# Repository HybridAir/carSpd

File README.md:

# carSpd

The carSpd (name in progress) is a work in progress device used to display your car's speed and other data in an easy to read, digital format. To do this, the device takes advantage of your car's speed and injector signals, much like the [MPGuino](http://ecomodder.com/wiki/index.php/MPGuino) project. Planned features include imperial/metric support, gas mileage and time display, and probably more depending on feature creep.

My main motivation for starting this project is so that I wont have to read the tiny kph numbers on my car's speedometer, since I just moved to Canada from the US with my car.

*This project is meant to be some kind of successor to the canceled carbt_v1 project. While their main functions are very different, they both serve the purpose of improving or adding new functions to my car.*

## Todo
- Finish programming
- Documentation
- Assemble

## Used Libraries
[Button](https://github.com/JChristensen/Button)

[EEPROMEx](https://github.com/thijse/Arduino-EEPROMEx)

[ST7032](https://github.com/tomozh/arduino_ST7032)

[RTC](https://github.com/Makuna/Rtc)

[RunningAverage](https://github.com/RobTillaart/Arduino/tree/master/libraries/RunningAverage)

[OneWire](https://github.com/PaulStoffregen/OneWire)

[DallasTemperature](https://github.com/milesburton/Arduino-Temperature-Control-Library)

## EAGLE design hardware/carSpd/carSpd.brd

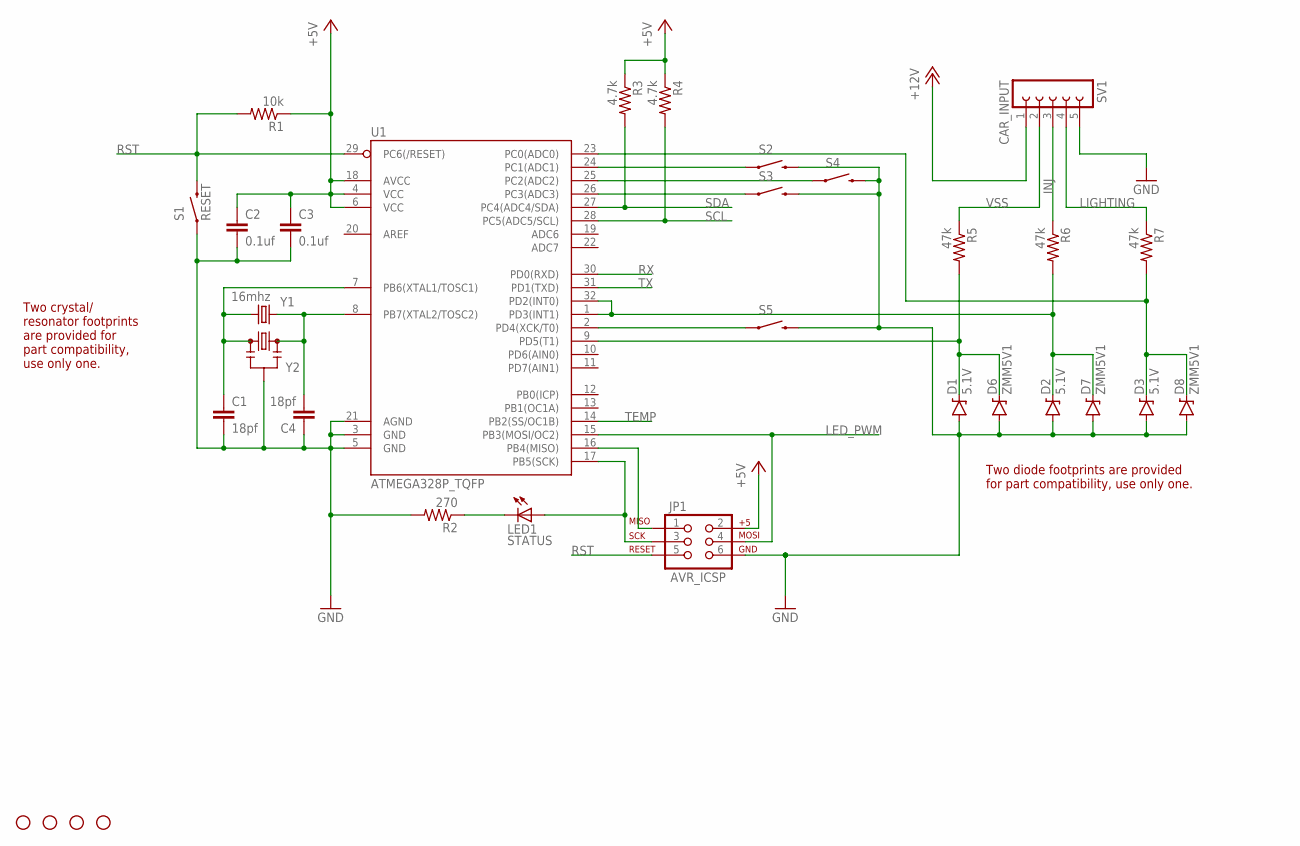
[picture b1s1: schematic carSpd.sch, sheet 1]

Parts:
C1, C4: 18pf; C0603K
C2, C3: 0.1uf; C0603K
D1, D2, D3: 5.1V; SOD-323
D6, D7, D8: ZMM5V1; SOD-80
H1, H2, H3, H4: STAND-OFF
JP1: AVR_ICSP; 2X3_TEST_POINTS
LED1: STATUS; CHIPLED_0805
R1: 10k; R0603
R2: 270; R0603
R3, R4: 4.7k; R0805
R5, R6, R7: 47k; R0805
S1: RESET; TACTILE-SWITCH-1101NE
S2, S3, S4, S5: SWITCH-MOMENTARY-2SMD-1101NE; TACTILE-SWITCH-1101NE
SV1: CAR_INPUT; FE05W
U1: ATMEGA328P_TQFP; TQFP32-08
Y1: 16mhz; CRYSTAL-SMD-5X3
Y2: 16MHZ; RESONATOR-SMD

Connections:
+5V: C2.1, C3.1, JP1.2, R1.1, R3.1, R4.1, U1.4 (VCC), U1.6 (VCC), U1.18 (AVCC); also elsewhere on the board
+12V: SV1.1; also elsewhere on the board
GND: C1.2, C2.2, C3.2, C4.1, D1.A, D2.A, D3.A, D6.A, D7.A, D8.A, JP1.6, R2.2, S1.1, S2.2, S3.2, S4.2, S5.2, SV1.5, U1.3 (GND), U1.5 (GND), U1.21 (AGND), Y2.2; also elsewhere on the board
INJ: R6.1, SV1.3
LED_PWM: JP1.4, U1.15 (PB3(MOSI/OC2)); also elsewhere on the board
LIGHTING: R7.1, SV1.4
unnamed: S2.1, U1.24 (PC1(ADC1))
unnamed: S4.1, U1.25 (PC2(ADC2))
unnamed: S3.1, U1.26 (PC3(ADC3))
unnamed: S5.1, U1.2 (PD4(XCK/T0))
unnamed: JP1.1, U1.16 (PB4(MISO))
unnamed: C1.1, U1.7 (PB6(XTAL1/TOSC1)), Y1.3 (2), Y2.1
unnamed: JP1.3, LED1.A, U1.17 (PB5(SCK))
unnamed: D2.C, D7.C, R6.2, U1.1 (PD3(INT1)), U1.32 (PD2(INT0))
unnamed: D3.C, D8.C, R7.2, U1.23 (PC0(ADC0))
unnamed: LED1.C, R2.1
unnamed: D1.C, D6.C, R5.2, U1.9 (PD5(T1))
unnamed: C4.2, U1.8 (PB7(XTAL2/TOSC2)), Y1.1, Y2.3
RST: JP1.5, R1.2, S1.2, U1.29 (PC6(/RESET)); also elsewhere on the board
RX: U1.30 (PD0(RXD)); also elsewhere on the board
SCL: R4.2, U1.28 (PC5(ADC5/SCL)); also elsewhere on the board
SDA: R3.2, U1.27 (PC4(ADC4/SDA)); also elsewhere on the board
TEMP: U1.14 (PB2(SS/OC1B)); also elsewhere on the board
TX: U1.31 (PD1(TXD)); also elsewhere on the board
VSS: R5.1, SV1.2

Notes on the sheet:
Two diode footprints are provided for part compatibility, use only one.
Two crystal/ resonator footprints are provided for part compatibility, use only one.

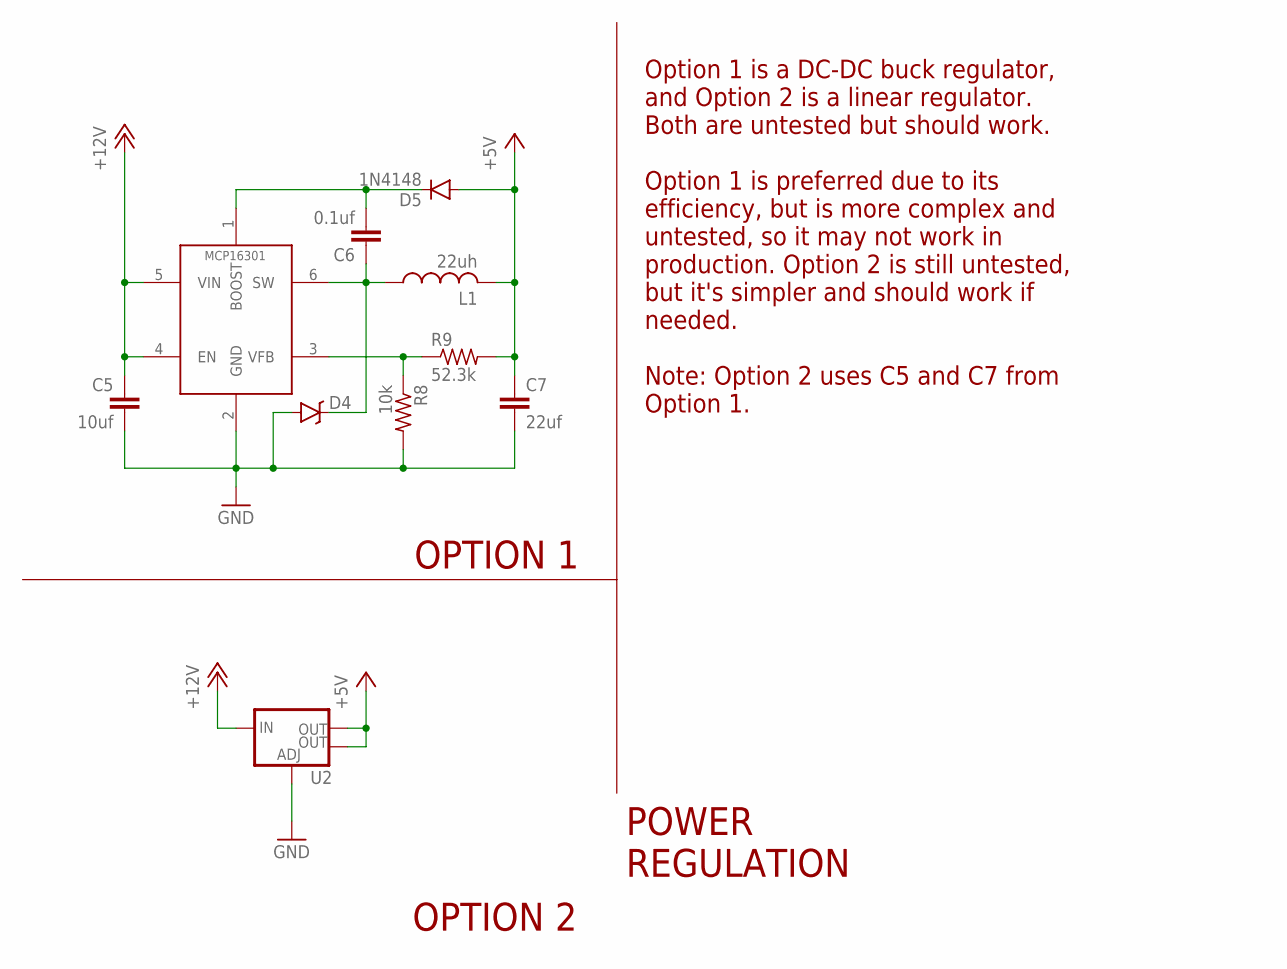
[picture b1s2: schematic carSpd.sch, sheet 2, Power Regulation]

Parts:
C5: 10uf; C0603K
C6: 0.1uf; C0603K
C7: 22uf; C0603K
D4: DIODE-SCHOTTKY-BAT20J; SOD-323
D5: 1N4148; SOD-323
IC1: MCP16301/H; SOT23-6
L1: 22uh; IND-1007/2518
R8: 10k; R0603
R9: 52.3k; R0603
U2: V_REG_LM1117SOT223; SOT223

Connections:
+5V: C7.1, D5.A, L1.P$2 (2), R9.2, U2.2 (OUT), U2.4 (OUT); also elsewhere on the board
+12V: C5.1, IC1.4 (EN), IC1.5 (VIN), U2.3 (IN); also elsewhere on the board
GND: C5.2, C7.2, D4.A, IC1.2 (GND), R8.2, U2.1 (ADJ); also elsewhere on the board
unnamed: IC1.3 (VFB), R8.1, R9.1
unnamed: C6.1, D4.C, IC1.6 (SW), L1.P$1 (1)
unnamed: C6.2, D5.C, IC1.1 (BOOST)

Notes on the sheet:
POWER REGULATION
Option 1 is a DC-DC buck regulator, and Option 2 is a linear regulator. Both are untested but should work. Option 1 is preferred due to its efficiency, but is more complex and untested, so it may not work in production. Option 2 is still untested, but it's simpler and should work if needed. Note: O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
OPTION 1
OPTION 2
MCP16301

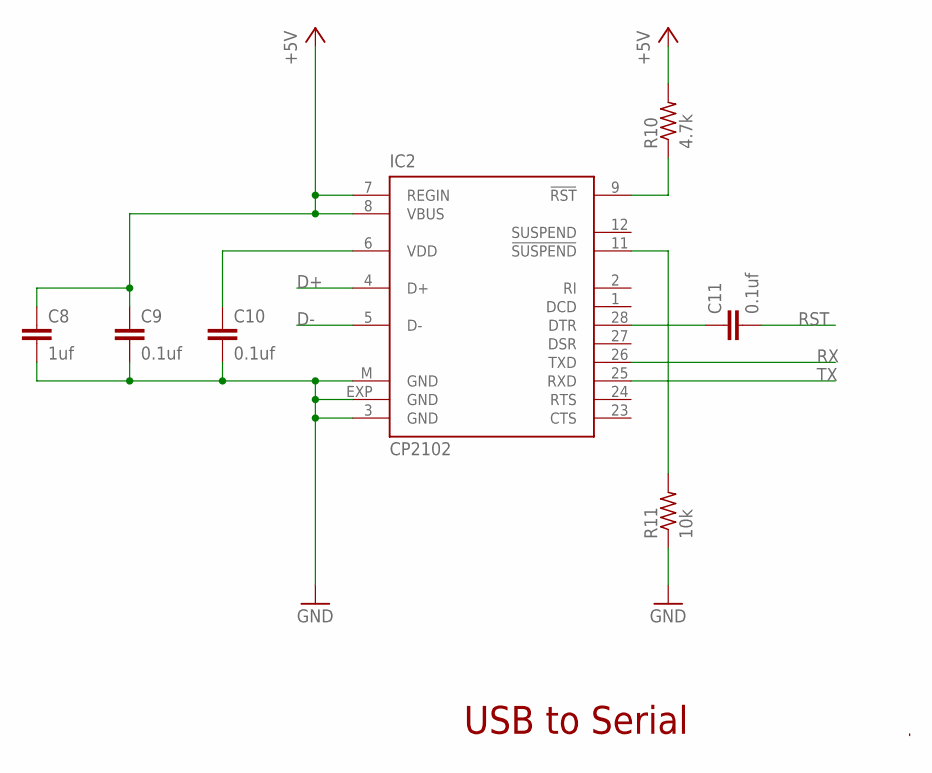
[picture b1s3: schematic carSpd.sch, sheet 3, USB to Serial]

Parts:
C8: 1uf; C0805K
C9, C10, C11: 0.1uf; C0603K
IC2: CP2102; MLP28
R10: 4.7k; R0805
R11: 10k; R0603

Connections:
+5V: C8.1, C9.1, IC2.7 (REGIN), IC2.8 (VBUS), R10.2; also elsewhere on the board
D+: IC2.4 (D+); also elsewhere on the board
D-: IC2.5 (D-); also elsewhere on the board
GND: C8.2, C9.2, C10.2, IC2.3 (GND), IC2.EXP (GND), IC2.M (GND), R11.1; also elsewhere on the board
unnamed: IC2.9 (!RST), R10.1
unnamed: IC2.11 (!SUSPEND), R11.2
unnamed: C11.1, IC2.28 (DTR)
unnamed: C10.1, IC2.6 (VDD)
RST: C11.2; also elsewhere on the board
RX: IC2.26 (TXD); also elsewhere on the board
TX: IC2.25 (RXD); also elsewhere on the board

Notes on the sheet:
USB to Serial

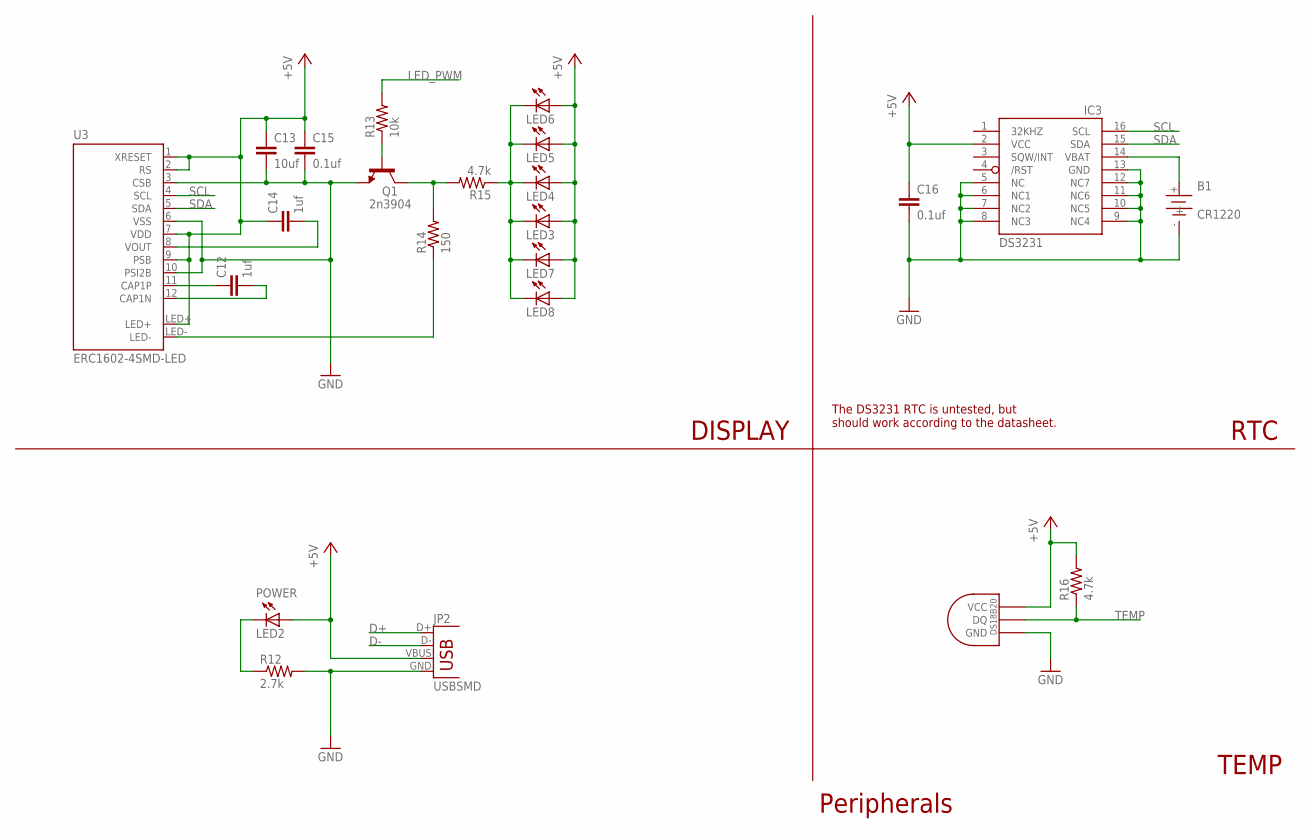
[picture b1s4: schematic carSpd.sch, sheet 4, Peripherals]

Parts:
B1: CR1220; 1220-SMD
C12, C14: 1uf; C0805K
C13: 10uf; C0603K
C15, C16: 0.1uf; C0603K
IC3: DS3231/SO; SO16W
JP2: USBSMD; USB-MINIB
LED2: POWER; CHIPLED_0805
LED3, LED4, LED5, LED6, LED7, LED8: LEDCHIPLED_0805; CHIPLED_0805
Q1: 2n3904; SOT23-3
R12: 2.7k; R0603
R13: 10k; R0603
R14: 150; R0603
R15, R16: 4.7k; R0805
U3: ERC1602-4SMD-LED; ERC1602-4_SMDLED
U4: DS1820; µSOP8

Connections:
+5V: C13.1, C14.1, C15.1, C16.1, IC3.2 (VCC), JP2.VBUS, LED2.A, LED3.A, LED4.A, LED5.A, LED6.A, LED7.A, LED8.A, R16.2, U3.1 (XRESET), U3.2 (RS), U3.7 (VDD), U3.9 (PSB), U3.LED+, U4.8 (VCC); also elsewhere on the board
D+: JP2.D+; also elsewhere on the board
D-: JP2.D-; also elsewhere on the board
GND: B1.-, C13.2, C15.2, C16.2, IC3.5 (NC), IC3.6 (NC1), IC3.7 (NC2), IC3.8 (NC3), IC3.9 (NC4), IC3.10 (NC5), IC3.11 (NC6), IC3.12 (NC7), IC3.13 (GND), JP2.GND, Q1.2 (E), R12.2, U3.3 (CSB), U3.6 (VSS), U3.10 (PSI2B), U4.4 (GND); also elsewhere on the board
LED_PWM: R13.2; also elsewhere on the board
unnamed: LED3.C, LED4.C, LED5.C, LED6.C, LED7.C, LED8.C, R15.1
unnamed: LED2.C, R12.1
unnamed: Q1.1 (B), R13.1
unnamed: C14.2, U3.8 (VOUT)
unnamed: Q1.3 (C), R14.2, R15.2
unnamed: R14.1, U3.LED-
unnamed: C12.1, U3.11 (CAP1P)
unnamed: C12.2, U3.12 (CAP1N)
unnamed: B1.+, IC3.14 (VBAT)
SCL: IC3.16 (SCL), U3.4 (SCL); also elsewhere on the board
SDA: IC3.15 (SDA), U3.5 (SDA); also elsewhere on the board
TEMP: R16.1, U4.1 (DQ); also elsewhere on the board

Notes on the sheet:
DISPLAY
RTC
TEMP
Peripherals
The DS3231 RTC is untested, but should work according to the datasheet.

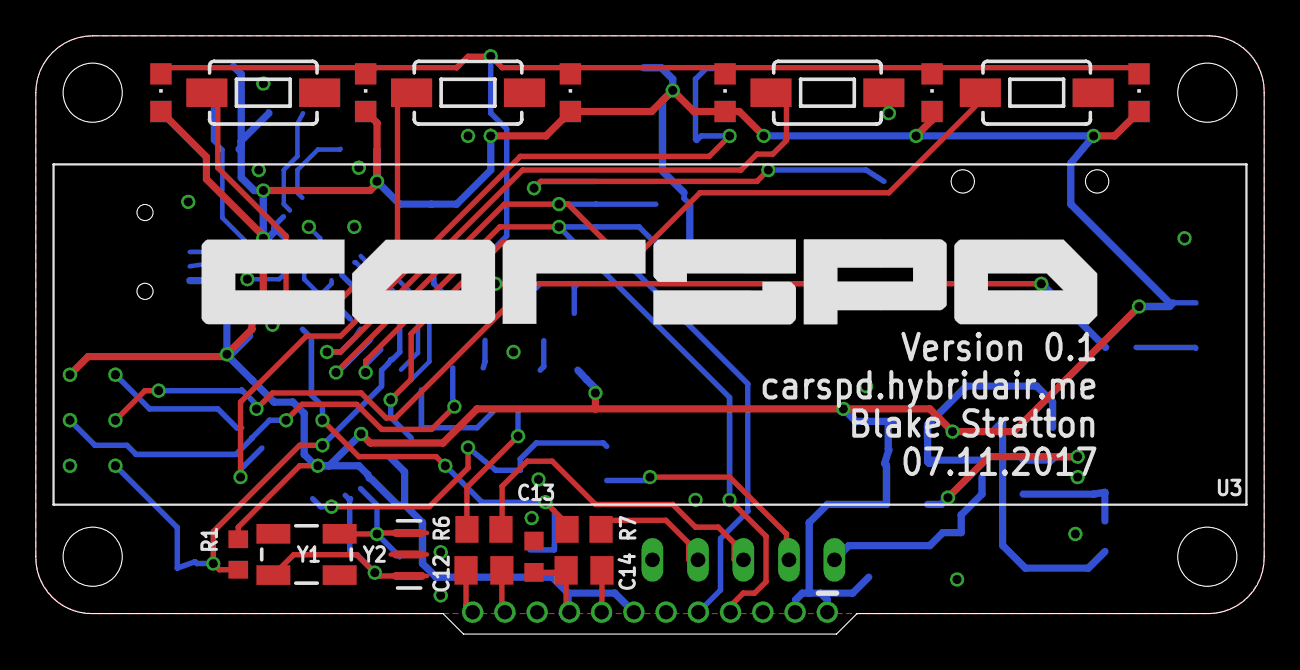
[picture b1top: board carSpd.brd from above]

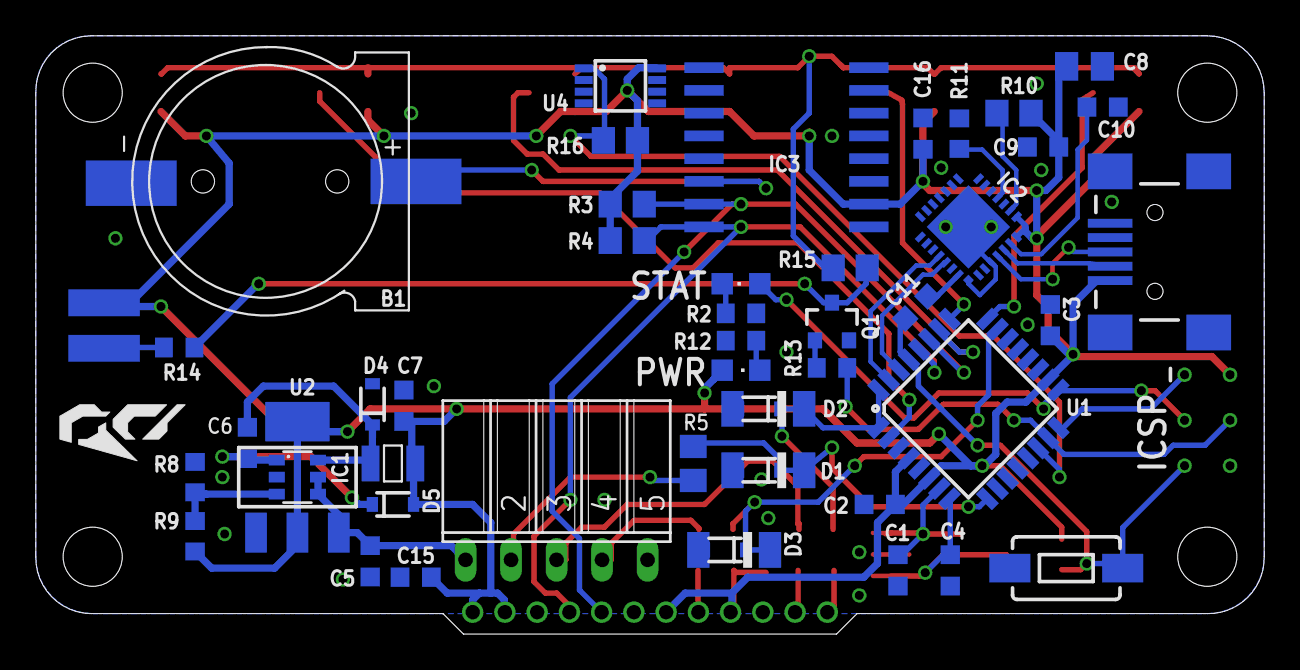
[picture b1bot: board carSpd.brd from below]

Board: 2 copper layers, 68.6 x 33.4 mm, 74 parts (50 on the bottom side), 43 nets.

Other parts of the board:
U$1: AR1
U$2: CARSPD

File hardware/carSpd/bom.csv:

Have,Qty,Device,Value,Package,Parts,Description
0,1,DS1820,DS1820,µSOP8,U4,DS18B20
0,1,DS3231/SO,DS3231/SO,SO16W,IC3,
0,3,Zener Diode ZMM5V1,5.1V,SOD-80,"D6, D7, D8",Backup diode package
1,1,resistor,150,603,R8,
1,1,resistor,270,603,R2,
1,8,capacitor,0.1uf/100nf,805,"C2, C3, C6, C9, C10, C11, C15, C16","CAPACITOR, European symbol"
1,1,resistor,100k,805,R2,
1,4,resistor,10k,603,"R1, R5, R7, R11",
1,1,capacitor,10nf,805,C5,
1,3,capacitor,10uf,603,"C1, C18, C7",
1,3,capacitor,1uf,805,"C8, C12, C14",
1,1,resistor,2.7k,603,R12,
1,1,transistor,2n3904,SOT23-3,Q1,Generic NPN BJT
1,5,resistor,4.7k,805,"R3, R4, R10, R15, R16",
1,3,resistor,47k,805,"R5, R6, R7",
1,1,ATMEGA328P-AU,ATMEGA328P_TQFP,TQFP32-08,U1,
1,1,Battery holder,CR1220,1220-SMD,B1,
1,1,Display,ERC1602-4SMD-LED,ERC1602-4,U3,ERC1602-4 LCD from buydisplay
1,1,led,green,805,LED2,Power led
1,1,led,red,CHIPLED_0805,LED1,status led
1,4,LED,white,805,"LED3, LED4, LED5, LED6",Button indicator LEDs
1,5,tactile button,,TACTILE-SWITCH-1101NE,"S1, S2, S3, S4, S5",Front and back reset buttons
1,1,serial to usb CP2102,CP2102,MLP28,IC2,Single-Chip USB to UART Bridge
+,1,6pin male header,CAR_INPUT,".1"" pth right angle",SV1,
+,1,inductor,22uh,L3225M,L1,
+,1,RESONATOR,16MHZ,RESONATOR-SMD,Y2,Resonator
+,1,CRYSTAL,16MHZ,CRYSTAL-SMD-5X3,Y1,Various standard crystals. Proven footprints.
+,2,capacitor,18pf,603,"C1, C4","CAPACITOR, European symbol"
+,3,Zener Diode,5.1V,SOD-323,"D1, D2, D3",Zener Diode
+,1,mini usb female,USBSMD,USB-MINIB,JP2,USB Connectors
+,1,capacitor,22uf,0603/0805,C7,
+,1,resistor,52.3k,603,R9,
+,1,DIODE-SCHOTTKY,,SOD-323,D4,
+,1,LM1117,,SOT223,U2,Linear voltage reg
+,1,Diode,1N4148,SOD-323,D5,
+,1,MCP16301/H,MCP16301/H,SOT23-6,IC1,High-Voltage Input Integrated Switch Step-Down Regulator

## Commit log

2017-06-15 Initial creation
2017-06-15 push test
2017-06-16 Init
2017-06-16 Added used library list
2017-06-16 yeah
2017-06-21 Added eeprom test code
2017-06-21 Added EEPROM support
2017-06-21 Added manual eeprom reset functionality
2017-06-22 Added todo list and library
2017-06-22 Cleanup
2017-06-22 Updated header file types
2017-06-23 Added manual backlight control
2017-06-23 Fixed
2017-06-23 Added automatic backlight control
2017-06-24 Added a temperature sensor
2017-06-29 Updated platforms, moved everything over to a bare atmega328p + optiboot
2017-06-30 Updated todo
2017-07-01 Added power regulator schematics
2017-07-01 Added USB to serial schematics
2017-07-01 Added peripheral schematics
2017-07-02 Finished schematic, unverified
2017-07-02 removing
2017-07-02 removing another file
2017-07-02 unused
2017-07-02 Removed the CH340G, supporting parts made it cost as much as a CP2102
2017-07-02 Schematic cleanup
2017-07-03 Modified and added parts list
2017-07-05 Replaced power regulator circuits
2017-07-05 Updated bom
2017-07-05 Part listing complete
2017-07-05 Corrected and verified schematics
2017-07-06 Moved
2017-07-06 Added digikey part numbers
2017-07-08 Routing complete
2017-07-09 Finished optimizations
2017-07-12 PCB design complete
2017-07-20 Remapped buttons
2017-07-20 Fixed button pin assignments
2017-07-20 Started boot animation progress
2017-07-22 Cleanup and big number implementation
2017-07-22 Cleaned up big number code
2017-07-23 Finished boot animation
2017-07-28 Cleanup and commenting
2017-07-28 Preparing to implement view system
2017-07-29 Began moving speed display over to a separate class
2017-07-30 Added update timer bypass for unit changes
2017-07-30 Added negative x value handling
2017-07-30 Cleanup, added speed unit display, and finished speed display
2017-07-30 Usable program with basic functionality (speed view only)
2017-08-29 Fixed speed calc math
2017-09-04 Ugly code that barely works (going to fix)
2017-09-05 Made the 1 look less like a 7
2017-09-05 Changed splash text
2017-09-06 Fixed speed calc
2017-09-08 Completely redone speed calc code

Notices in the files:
parts and their libraries:
SparkFun-Electromechanical: Licensing: Creative Commons ShareAlike 4.0 International - https://creativecommons.org/licenses/by-sa/4.0
